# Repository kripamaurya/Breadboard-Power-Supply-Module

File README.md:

# ⚡ Breadboard Power Supply Module

> A compact and efficient breadboard power supply module designed in KiCad, providing stable **5V** and **3.3V** regulated outputs for electronics prototyping and embedded projects.

---

## 🚀 Features

✅ Dual regulated outputs (5V & 3.3V)

✅ AMS1117 Voltage Regulators

✅ DC Barrel Jack Power Input

✅ Power Status LEDs

✅ Filter Capacitors for Stable Output

✅ Breadboard Compatible Design

✅ Compact PCB Layout

---

## 🛠 Hardware Used

| Component | Quantity |
|------------|----------|
| AMS1117-5.0 | 1 |
| AMS1117-3.3 | 1 |
| DC Barrel Jack | 1 |
| LEDs | 3 |
| Resistors | 3 |
| Capacitors | 6 |
| Pin Headers | 2 |

---

## 📂 Repository Structure

```text
Breadboard-Power-Supply-Module/
│
├── Schematic/
├── PCB/
├── Gerber_Files/
├── Images/
├── BOM.csv
├── LICENSE
└── README.md
```

---

## 🔧 Software Used

- KiCad 9.0
- PCB Editor
- 3D Viewer

---

## 📋 Design Flow

1. Circuit Design
2. Schematic Capture
3. PCB Layout Design
4. Component Placement
5. PCB Routing
6. 3D Visualization
7. Gerber Generation

---

## 🎯 Applications

- Breadboard Prototyping
- Arduino Projects
- ESP32 Projects
- Embedded Systems
- IoT Development
- Electronics Learning

---

## 📸 Additional Views

---

## 📄 License

This project is licensed under the MIT License.

---

## 👨‍💻 Author

**TSAR INDUSTRY ©**

If you found this project useful, consider giving it a ⭐ on GitHub.

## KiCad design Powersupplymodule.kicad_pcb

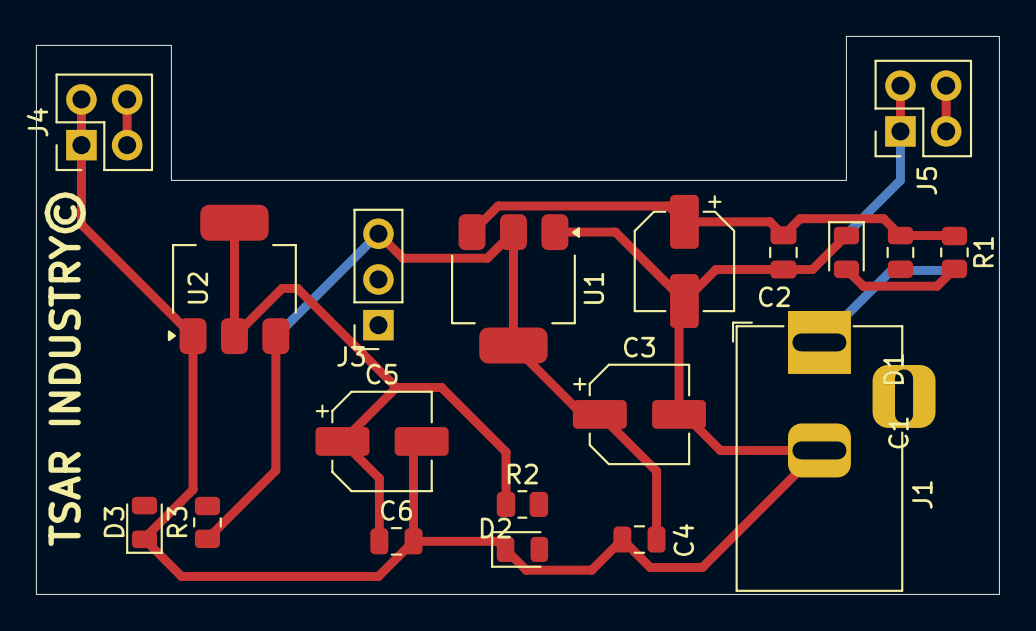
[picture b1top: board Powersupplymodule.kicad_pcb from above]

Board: 2 copper layers, 53.5 x 31.0 mm, 19 parts (0 on the bottom side), 10 nets.

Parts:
C1, C3, C5: 100uF; CP_Elec_5x5.8
C2, C4, C6: 0.1uf; C_0805_2012Metric
D1, D2, D3: GREEN_LED; LED_0805_2012Metric
F1: Fuse; Fuse_0805_2012Metric
J1: Barrel_Jack_Switch; BarrelJack_Horizontal
J3: Conn_01x03_Pin; PinSocket_1x03_P2.54mm_Vertical
J4, J5: Conn_02x02_Odd_Even; PinHeader_2x02_P2.54mm_Vertical
R1: 1K; R_0805_2012Metric
R2: 330; R_0805_2012Metric
R3: 560; R_0805_2012Metric
U1: AMS1117-5.0; SOT-223-3_TabPin2
U2: AMS1117-3.3; SOT-223-3_TabPin2

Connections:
GND: C1.2, C2.2, C3.2, C4.2, C5.2, C6.2, D1.1 (K), D2.1 (K), D3.1 (K), J1.2, J4.1, J4.2, J5.1, J5.2, U1.1 (GND), U2.1 (GND)
unnamed: D1.2 (A), R1.2
unnamed: D2.2 (A), R2.2
unnamed: D3.2 (A), R3.2
unnamed: F1.1, J1.1
unnamed: C3.1, C4.1, J3.3 (Pin_3_3), R3.1, U1.2 (VO), U2.3 (VI)
unnamed: J4.3, J4.4
unnamed: J5.3, J5.4
unnamed: C1.1, C2.1, F1.2, R1.1, U1.3 (VI)
unnamed: C5.1, C6.1, R2.1, U2.2 (VO)
